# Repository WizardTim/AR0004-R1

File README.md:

# AR0004-R1
PCB design files for 10W D50/D65 (5000K/6500K ANSI approximate) standard illuminant modular LED panels. Note any 3528 PLCC LED will suffice provided forward voltage and maximum current are accounted for.

### Design Notes:
* Potentiometer mounts on LED side of PCB, reverse pins and deadzone resistor in schematic for opposite mounting
* Thermal design of PCB heatsinking for LEDs is insufficient to cool LEDs to a temperature to prolong life, external heatsink & active cooling required for operation at 10W.
* A diffusor is recommended to reduce intensity of reflections and ease eye strain. Folded printer paper can suffice but will reduce efficiency and minorly affect colour point/spectral content.

### Related Videos
* _**'SMT Design Mistakes'**_: [https://youtu.be/_iIPJBWDUq0](https://youtu.be/_iIPJBWDUq0) discusses heat conduction problems related to interrupted copper areas on a typical 1 oz FR-4 PCB.

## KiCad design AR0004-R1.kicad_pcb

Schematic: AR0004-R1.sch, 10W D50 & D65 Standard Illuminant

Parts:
C1, C2, C3, C4: 100n; R_0603
C5, C6, C7, C8: 10u; R_1210
C9, C14: 1u; R_1206
D1, D2, D3, D4, D5, D6, D7, D8, D9, D10, D12, D13, D14, D15, D16, D17, D18, D19, D20, D21: EAHC; LED_PLCC_2835
D11: Schottky; D_SMB
D22: BLUE; LED_0603
J1, J2: +; Test_Point_Keystone_5019_Minature
J3: 5.5mm; BARREL_JACK
J4, J5: -; Test_Point_Keystone_5019_Minature
J6: FAN; Pin_Header_Straight_1x02_Pitch2.54mm
L1: 33u; Choke_SMD_12x12mm_h4.5mm
MK1, MK2, MK3, MK4, MK5, MK6: M3 Mounting Hole; MountingHole_3.2mm_M3_ISO14580_Pad
R1: 2.7k; R_0603
R2, R3, R4: 0.1; R_1206
R5: 1k; R_0603
RV1: 10k; Potentiometer_Alps_RK09K_Vertical
U1: AP1117-33; SOT-223-3_TabPin2
U2: L7805; TO-252-2
U3: AL8843MP; HTSOP-8-1EP_3.9x4.9mm_Pitch1.27mm_ThermalVias_LargeCopper

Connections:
+3V3: C2.1, R1.1, R5.1, U1.2 (VO)
+5V: C4.1, J6.2, U2.3
GND: C1.1, C2.2, C3.1, C4.2, C5.2, C6.2, C7.2, C8.2, D22.1, J3.2, J3.3, J4.1, J5.1, J6.1, MK1.1, MK2.1, MK3.1, MK4.1, MK5.1, MK6.1, RV1.3, U1.1 (GND), U2.2, U3.1, U3.2, U3.9
LED+: C9.1, C14.1, D1.2, D2.2, D3.2, D4.2, D5.2, D6.2, D7.2, D8.2, D9.2, D10.2, D12.2, D13.2, D14.2, D15.2, D16.2, D17.2, D18.2, D19.2, D20.2, D21.2, R2.1, R3.1, R4.1, U3.3
LED-: C9.2, C14.2, D1.1, D2.1, D3.1, D4.1, D5.1, D6.1, D7.1, D8.1, D9.1, D10.1, D12.1, D13.1, D14.1, D15.1, D16.1, D17.1, D18.1, D19.1, D20.1, D21.1, L1.1
unnamed: D11.2, L1.2, U3.7, U3.8
unnamed: D22.2, R5.2
unnamed: R1.2, RV1.1
unnamed: RV1.2, U3.5
VCC: C1.2, C3.2, C5.1, C6.1, C7.1, C8.1, D11.1, J1.1, J2.1, J3.1, R2.2, R3.2, R4.2, U1.3 (VI), U2.1, U3.6

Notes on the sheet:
DC In
Daisy-Chain Connectors
3.3V Linear Regulator
5V Fan Linear Regulator
Power LED
LED Driver
LED Array
Current Sense
I =
0.1
______
Analog Dimming
C9 & C14 are optional for better smoothing
Everlight EAHC2835WD4 (5000K) & EAHC2835WD6 (6500K)
Design Calculations
Pin 5 (CTRL) of the AL8843 allows for dimming via either an analog voltage or PWM signal. The analog voltage control method is used in this design. Adjustment Range Input Range This Design The adjustment range in this design is greater than the input range to ensure full control reguardless of resi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
: 10 to 100% : 0.4 to 2.5 V : 0.0 to 2.6 V
10 uF capacitors must be 50V X7R
Pin 3 (SET) of the AL8843 is the input for a high side current sense shunt. This design uses a 0.033 ohm shunt to acheive 3 A average output current when dimming is at 100%. The nominal average output current can be configured using those formula
R2=R3=R4 = R×3 = 0.033×3 = 0.1
Vupper =
Vcc×RV1
___________
R1+RV1
3.3×10k
____________
2.7k+10k
= 2.598 V
0.033
= 3
All resistors 1% 250ppm unless specified All capacitors X7R unless specified

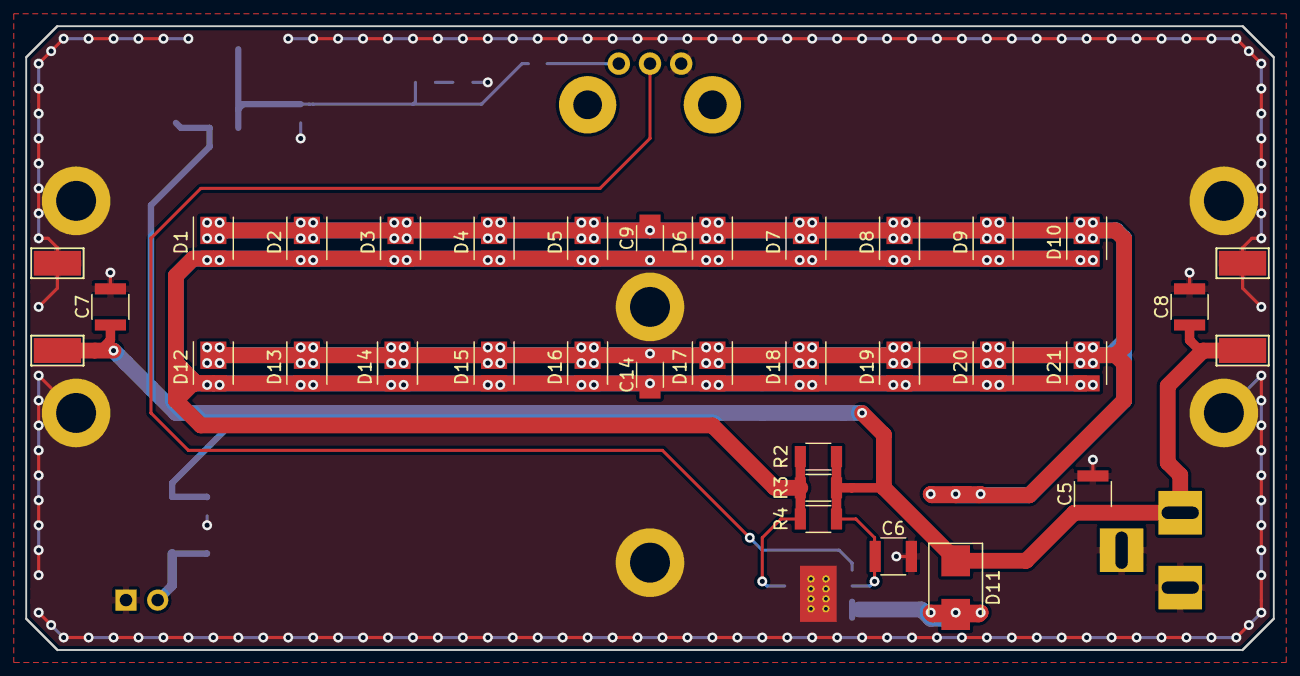
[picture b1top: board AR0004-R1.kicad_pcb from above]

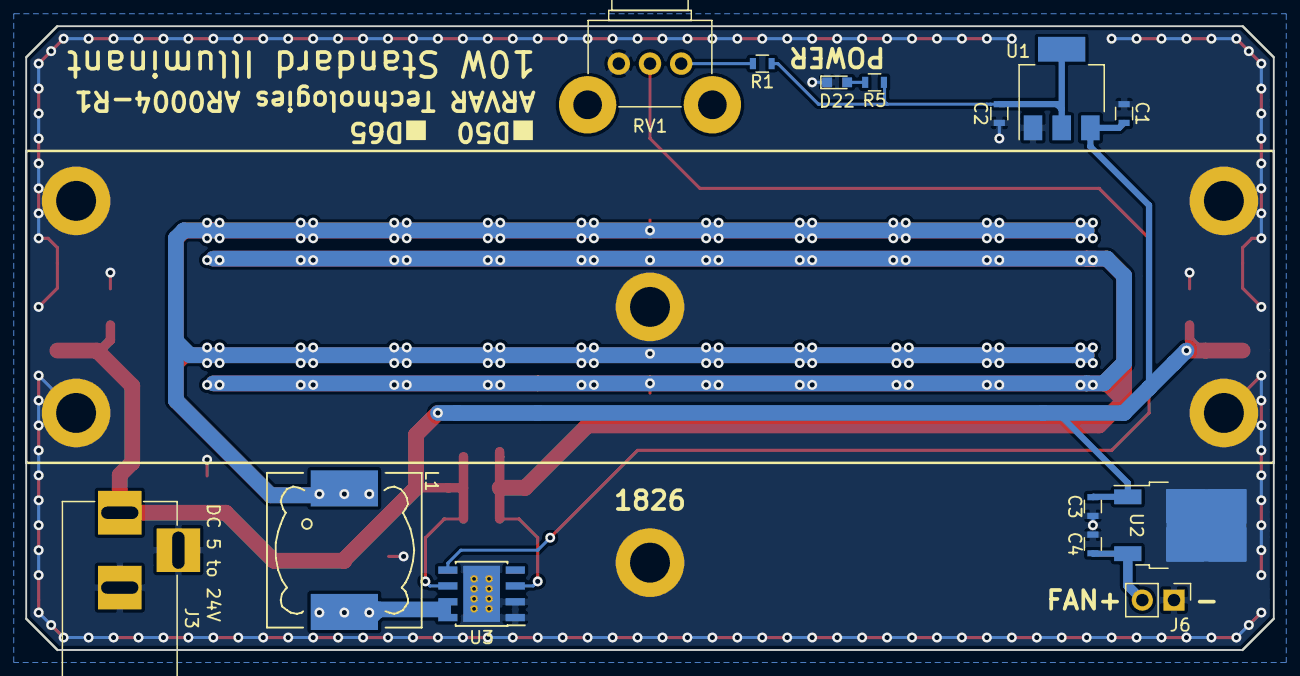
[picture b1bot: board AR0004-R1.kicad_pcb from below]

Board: 2 copper layers, 100.0 x 50.0 mm, 54 parts (14 on the bottom side), 10 nets.

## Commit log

2018-09-28 Uploaded project files
2019-01-27 Cleanup files
2020-08-31 Add image of assembled device
2020-08-31 Markdown rendering fix
2020-08-31 Typo + hyperlink
